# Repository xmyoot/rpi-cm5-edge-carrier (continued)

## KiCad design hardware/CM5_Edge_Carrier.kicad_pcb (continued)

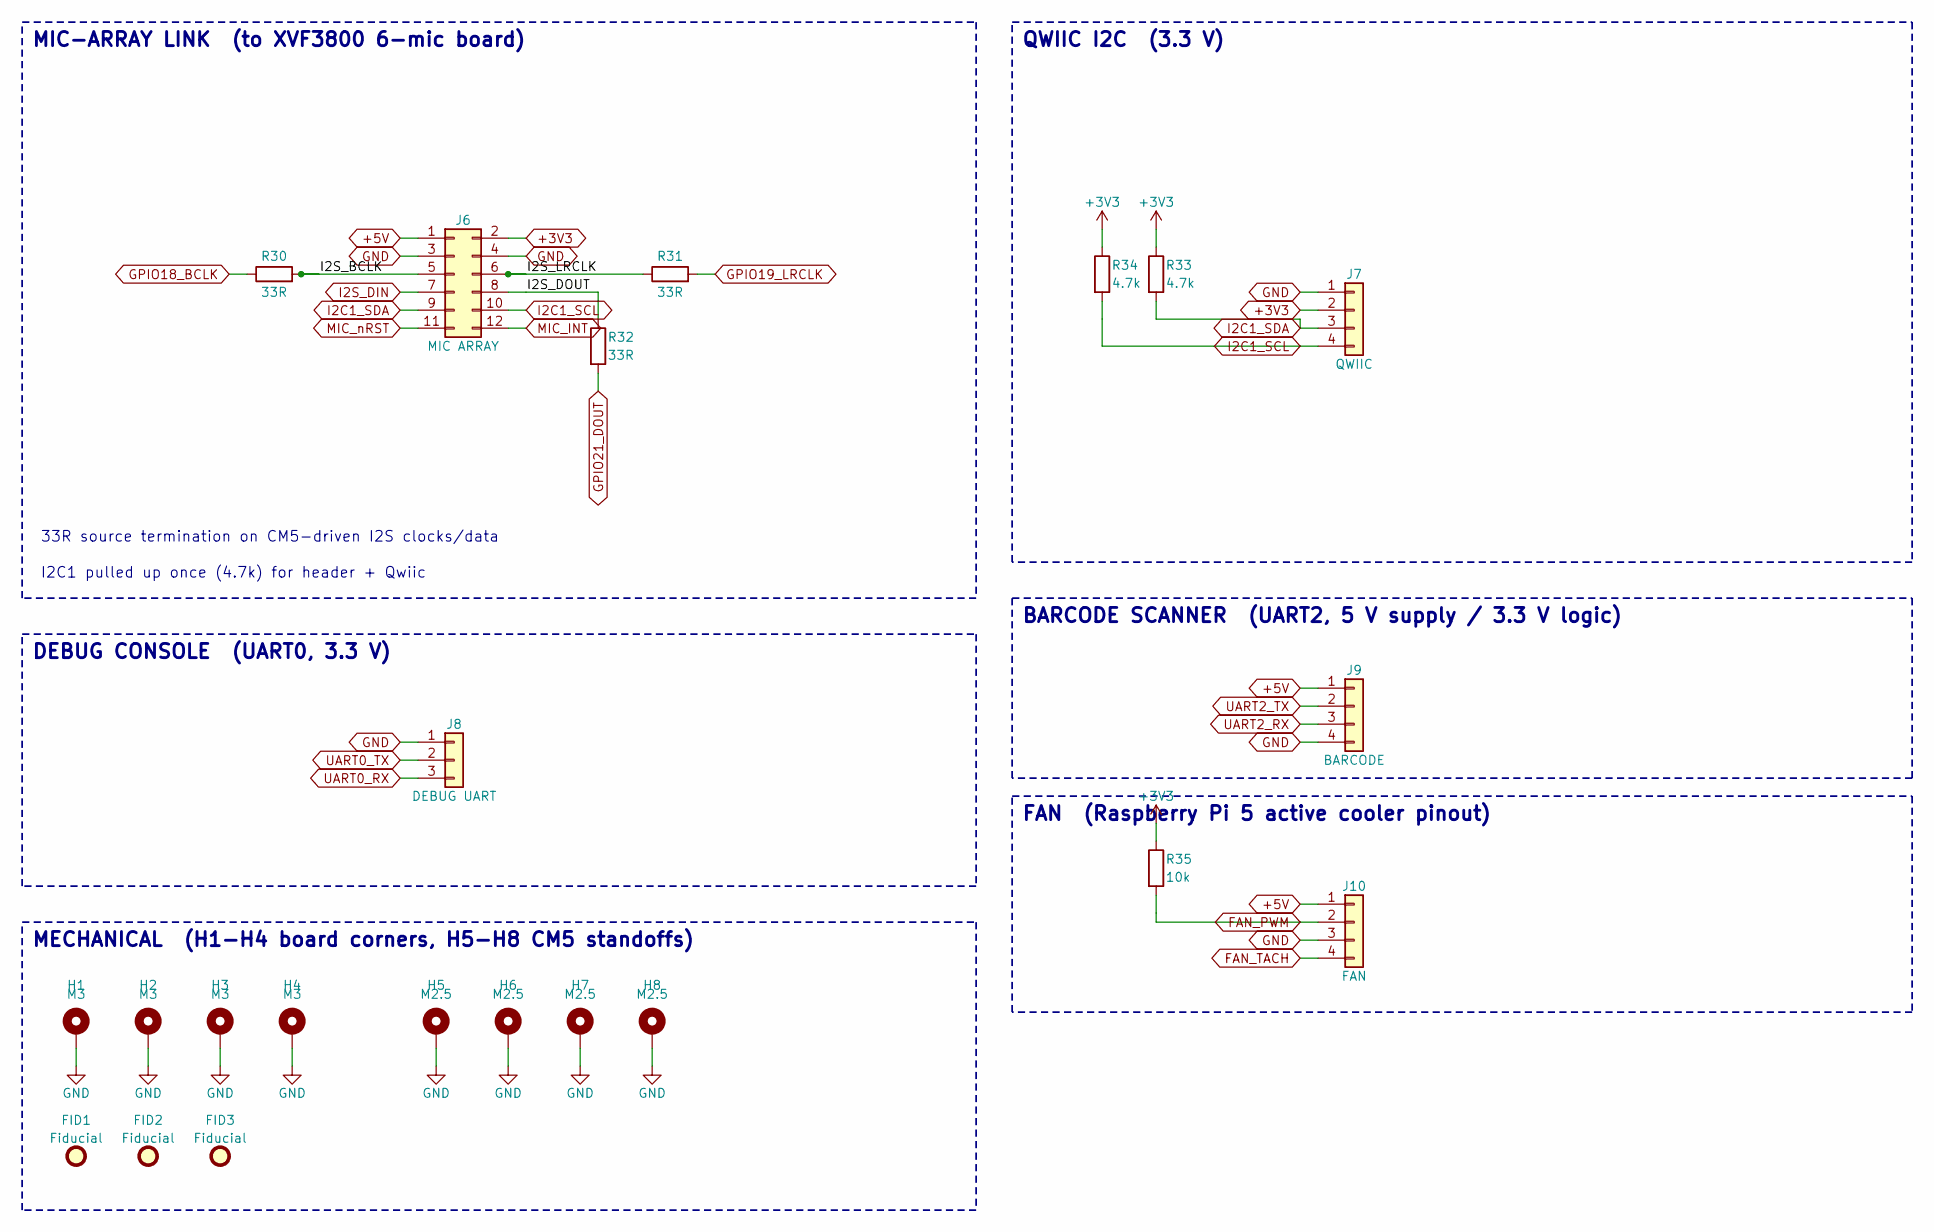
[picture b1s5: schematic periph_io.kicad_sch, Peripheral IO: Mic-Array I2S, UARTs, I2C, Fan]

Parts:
FID1, FID2, FID3: Fiducial; Fiducial_1mm_Mask2mm
H1, H2, H3, H4: M3; MountingHole_3.2mm_M3_Pad_Via
H5, H6, H7, H8: M2.5; MountingHole_2.7mm_M2.5_Pad_Via
J6: MIC ARRAY; IDC-Header_2x06_P2.54mm_Vertical; MPN 2x6 2.54 mm shrouded box header
J7: QWIIC; JST_SH_SM04B-SRSS-TB_1x04-1MP_P1.00mm_Horizontal; MPN JST SM04B-SRSS-TB; LCSC C160404
J8: DEBUG UART; PinHeader_1x03_P2.54mm_Vertical
J9: BARCODE; JST_SH_SM04B-SRSS-TB_1x04-1MP_P1.00mm_Horizontal; MPN JST SM04B-SRSS-TB; LCSC C160404
J10: FAN; JST_SH_SM04B-SRSS-TB_1x04-1MP_P1.00mm_Horizontal; MPN JST SM04B-SRSS-TB; LCSC C160404
R30, R31, R32: 33R; R_0402_1005Metric; Tolerance 1%; LCSC C25105
R33, R34: 4.7k; R_0402_1005Metric; Tolerance 1%; LCSC C25900
R35: 10k; R_0402_1005Metric; Tolerance 1%; LCSC C25744

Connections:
+3V3: J6.2, J7.2, R33.1, R34.1, R35.1; also elsewhere on the board
+5V: J6.1, J9.1, J10.1; also elsewhere on the board
/PeriphIO/I2S_BCLK: J6.5, R30.2
/PeriphIO/I2S_DOUT: J6.8, R32.1
/PeriphIO/I2S_LRCLK: J6.6, R31.1
FAN_PWM: J10.2, R35.2; also elsewhere on the board
FAN_TACH: J10.4; also elsewhere on the board
GND: H1.1, H2.1, H3.1, H4.1, H5.1, H6.1, H7.1, H8.1, J6.3, J6.4, J7.1, J8.1, J9.4, J10.3; also elsewhere on the board
GPIO18_BCLK: R30.1; also elsewhere on the board
GPIO19_LRCLK: R31.2; also elsewhere on the board
GPIO21_DOUT: R32.2; also elsewhere on the board
I2C1_SCL: J6.10, J7.4, R34.2; also elsewhere on the board
I2C1_SDA: J6.9, J7.3, R33.2; also elsewhere on the board
I2S_DIN: J6.7; also elsewhere on the board
MIC_INT: J6.12; also elsewhere on the board
MIC_nRST: J6.11; also elsewhere on the board
UART0_RX: J8.3; also elsewhere on the board
UART0_TX: J8.2; also elsewhere on the board
UART2_RX: J9.3; also elsewhere on the board
UART2_TX: J9.2; also elsewhere on the board

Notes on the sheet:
MIC-ARRAY LINK (to XVF3800 6-mic board)
QWIIC I2C (3.3 V)
DEBUG CONSOLE (UART0, 3.3 V)
BARCODE SCANNER (UART2, 5 V supply / 3.3 V logic)
FAN (Raspberry Pi 5 active cooler pinout)
MECHANICAL (H1-H4 board corners, H5-H8 CM5 standoffs)
33R source termination on CM5-driven I2S clocks/data
I2C1 pulled up once (4.7k) for header + Qwiic

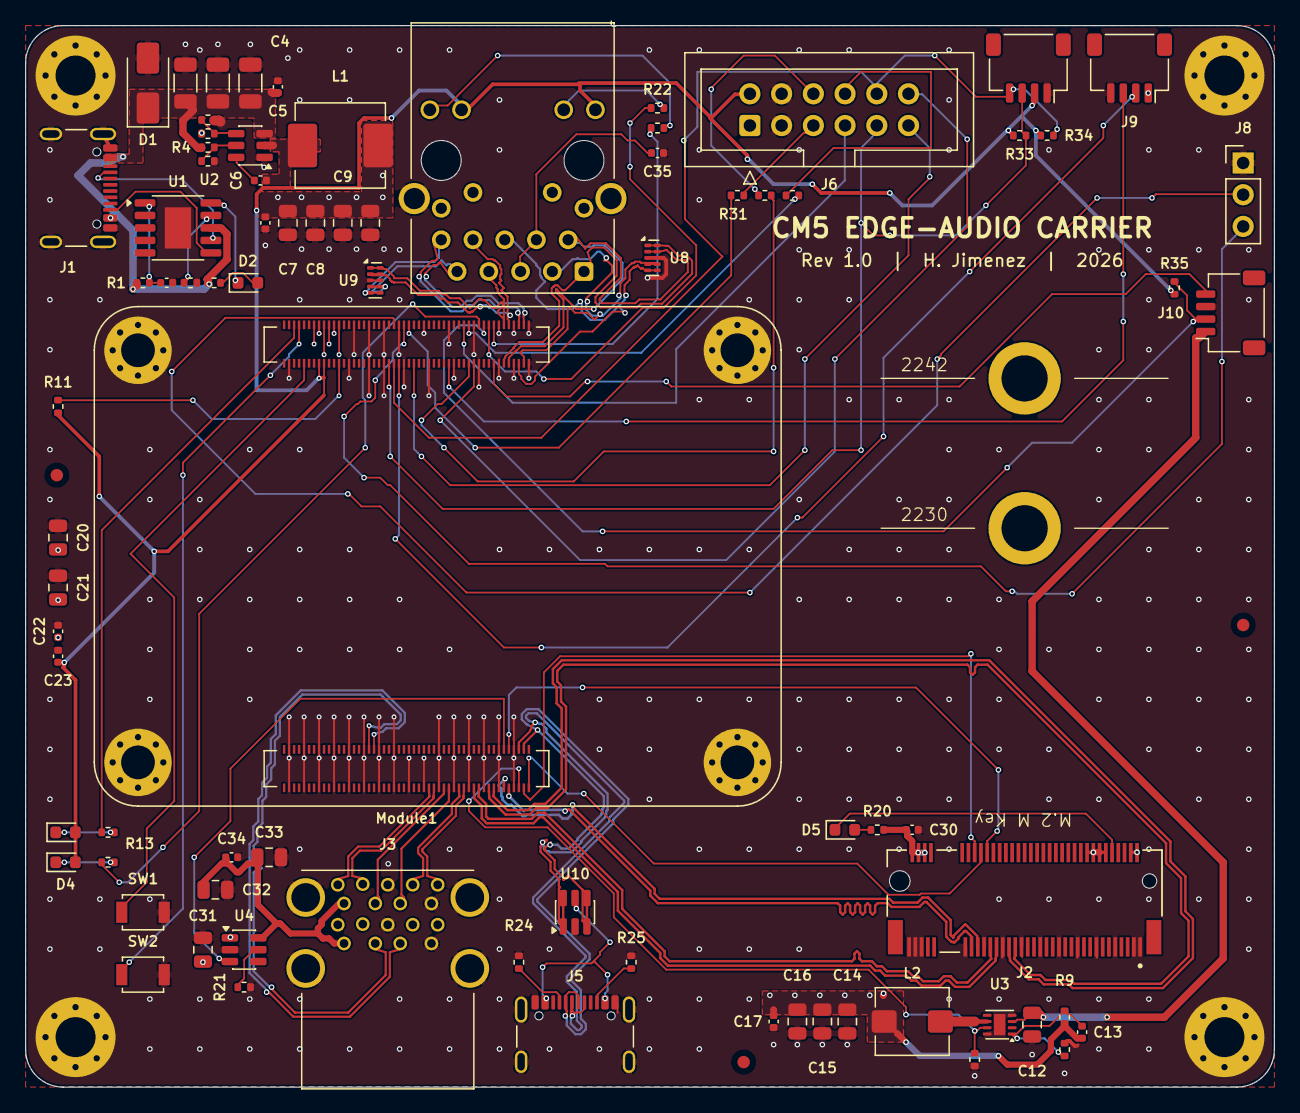
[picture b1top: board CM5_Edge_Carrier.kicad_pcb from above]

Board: 4 copper layers, 100.0 x 85.0 mm, 90 parts (0 on the bottom side), 82 nets.

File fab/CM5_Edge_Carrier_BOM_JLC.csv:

Comment,Designator,Footprint,Quantity,Manufacturer Part,JLCPCB Part #
22uF,"C1,C2,C4",C_1206_3216Metric,3,,C12891
1uF,C3,C_0402_1005Metric,1,,C52923
100nF,"C5,C6,C11,C17,C22,C23,C30,C34,C35",C_0402_1005Metric,9,,C1525
22uF,"C7,C8,C9,C10,C20,C21,C32,C33",C_0805_2012Metric,8,,C45783
10uF,"C12,C14,C15,C16,C31",C_0805_2012Metric,5,,C15850
4.7nF,C13,C_0402_1005Metric,1,,C1538
SMAJ15A,D1,D_SMA,1,Littelfuse SMAJ15A,
PD_OK,D2,LED_0603_1608Metric,1,,C72043
PWR (red),D3,LED_0603_1608Metric,1,,C2286
ACT (green),D4,LED_0603_1608Metric,1,,C72043
SSD (green),D5,LED_0603_1608Metric,1,,C72043
USB-C PD IN,J1,USB_C_Receptacle_GCT_USB4105-xx-A_16P_TopMnt_Horizontal,1,GCT USB4105-GF-A,C3020560
M.2 M-Key (NVMe 2230/2242),J2,M.2_M_Key_2242,1,MTCONN MTSSD03-67MSW337 (H=3.2 mm),
USB 3.0 A x2 (stacked),J3,MTCONN_UBAF30-D2011,1,MTCONN UBAF30-D2011,
RJ45 MagJack 1000BASE-T,J4,TRJG0926HENL,1,Trxcom TRJG0926HENL,
USB-C SERVICE,J5,USB_C_Receptacle_GCT_USB4105-xx-A_16P_TopMnt_Horizontal,1,GCT USB4105-GF-A,C3020560
MIC ARRAY,J6,IDC-Header_2x06_P2.54mm_Vertical,1,2x6 2.54 mm shrouded box header,
QWIIC,J7,JST_SH_SM04B-SRSS-TB_1x04-1MP_P1.00mm_Horizontal,1,JST SM04B-SRSS-TB,C160404
DEBUG UART,J8,PinHeader_1x03_P2.54mm_Vertical,1,,
BARCODE,J9,JST_SH_SM04B-SRSS-TB_1x04-1MP_P1.00mm_Horizontal,1,JST SM04B-SRSS-TB,C160404
FAN,J10,JST_SH_SM04B-SRSS-TB_1x04-1MP_P1.00mm_Horizontal,1,JST SM04B-SRSS-TB,C160404
2.2uH,L1,L_Sunlord_MWSA0603S,1,Sunlord MWSA0603S-2R2MT,
2.2uH,L2,L_Bourns_SRP5030T,1,Bourns SRP5030T-2R2M,
Raspberry Pi CM5,Module1,RPi_CM5_DF40,1,Raspberry Pi CM5 + 2x Hirose DF40C-100DS-0.4V(51),C597931 (x2)
1k,"R1,R12,R13,R20",R_0402_1005Metric,4,,C11702
24k,R2,R_0402_1005Metric,1,,
4.7k,"R3,R33,R34",R_0402_1005Metric,3,,C25900
100k,"R4,R8",R_0402_1005Metric,2,,C25741
15k,"R5,R21",R_0402_1005Metric,2,,C25756
56k,R6,R_0402_1005Metric,1,,C25796
10k,"R7,R9,R35",R_0402_1005Metric,3,,C25744
2.2k,R10,R_0402_1005Metric,1,,C25879
0R,R11,R_0402_1005Metric,1,,C17168
470R,"R22,R23",R_0402_1005Metric,2,,C25117
5.1k,"R24,R25",R_0402_1005Metric,2,,C25905
33R,"R30,R31,R32",R_0402_1005Metric,3,,C25105
POWER,SW1,SW_SPST_B3U-1000P,1,Omron B3U-1000P,C231329
nRPIBOOT,SW2,SW_SPST_B3U-1000P,1,Omron B3U-1000P,C231329
CH224K,U1,SSOP-10-1EP_3.9x4.9mm_P1mm_EP2.1x3.3mm,1,WCH CH224K,C970725
TPS565208,U2,SOT-23-6,1,TI TPS565208DDCR,
AP3441SHE-7B,U3,DFN-8-1EP_2x2mm_P0.5mm_EP0.9x1.7mm,1,Diodes AP3441SHE-7B,
AP22653W6,U4,SOT-23-6,1,Diodes AP22653W6-7,
TPD4EUSB30,"U8,U9",USON-10_2.5x1.0mm_P0.5mm,2,TI TPD4EUSB30DQAR,
USBLC6-2SC6,U10,SOT-23-6,1,ST USBLC6-2SC6,C7519

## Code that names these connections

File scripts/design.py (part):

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    ((332.74, 124.46), 'nRPIBOOT: hold while powering to enter USB boot;'),
    ((332.74, 129.54), 'flash eMMC from a host via USB-C SERVICE (rpiboot).'),
    ((332.74, 137.16), 'PWR_BUT: short press = wake / clean shutdown.'),
    ((332.74, 144.78), 'GPIO bank powered at 3.3 V (GPIO_VREF = +3V3).'),
    ((332.74, 152.4), 'Unused: HDMI0/1, MIPI0/1, SD (eMMC SKU), CAM_GPIO,'),
    ((332.74, 157.48), 'PMIC_ENABLE, EEPROM_nWP, WiFi/BT_nDisable, VBAT.'),
])
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    cm5[p] = 'GND'
for p in (77, 79, 81, 83, 85, 87):
    cm5[p] = '+5V'
cm5.update({84: '+3V3', 86: '+3V3', 78: 'GPIO_VREF',
            3: 'ETH_D3_P', 5: 'ETH_D3_N', 4: 'ETH_D1_P', 6: 'ETH_D1_N',
            9: 'ETH_D2_N', 11: 'ETH_D2_P', 10: 'ETH_D0_N', 12: 'ETH_D0_P',
            15: 'ETH_nLED3', 17: 'ETH_nLED2', 16: 'FAN_TACH', 19: 'FAN_PWM', 21: 'LED_nACT', 95: 'LED_nPWR',
            92: 'PWR_BUT', 93: 'nRPIBOOT',
            56: 'I2C1_SCL', 58: 'I2C1_SDA', 55: 'UART0_TX', 51: 'UART0_RX', 54: 'UART2_TX', 34: 'UART2_RX',
            49: 'GPIO18_BCLK', 26: 'GPIO19_LRCLK', 27: 'I2S_DIN', 25: 'GPIO21_DOUT', 24: 'MIC_INT', 48: 'MIC_nRST',
            103: 'USB2_N', 105: 'USB2_P', 111: 'VBUS_EN',
            102: 'PCIE_nCLKREQ', 104: 'PCIE_nWAKE', 106: 'PCIE_PWR_EN', 109: 'PCIE_nRST',
            110: 'PCIE_CLK_P', 112: 'PCIE_CLK_N', 116: 'PCIE_RX_P', 118: 'PCIE_RX_N', 122: 'PCIE_TX_P', 124: 'PCIE_TX_N',
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for i, (ref, val, net) in enumerate((('C20', '22uF', '+5V'), ('C21', '22uF', '+5V'), ('C22', '100nF', '+5V'),
                                      ('C23', '100nF', '+3V3'))):
    C(M, ref, val, G(10 + 5 * i, 15), net, 'GND')
R(M, 'R11', '0R', G(27, 78), '+3V3', 'GPIO_VREF', rot=90)
FLAG(M, '#FLG06', 'GPIO_VREF', G(22, 74))
R(M, 'R12', '1k', G(140, 16), 'LED_nPWR', 'LED_PWR_K', rot=90)
LED(M, 'D3', 'PWR (red)', G(147, 16), 'LED_PWR_K', '+3V3', 'C2286')
R(M, 'R13', '1k', G(140, 22), 'LED_nACT', 'LED_ACT_K', rot=90)
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            'Connector_IDC:IDC-Header_2x06_P2.54mm_Vertical', G(30, 22), hdr, pin_style={1: 'glabel', 2: 'glabel', 3: 'glabel', 4: 'glabel'},
            fields={'MPN': '2x6 2.54 mm shrouded box header'},
            desc='Mic-array (XVF3800) link: I2S + I2C control + reset/IRQ'))
R(I, 'R30', '33R', G(20, 22), 'GPIO18_BCLK', 'I2S_BCLK', rot=90)
R(I, 'R31', '33R', G(42, 22), 'I2S_LRCLK', 'GPIO19_LRCLK', rot=90)
R(I, 'R32', '33R', G(38, 26), 'I2S_DOUT', 'GPIO21_DOUT')
R(I, 'R33', '4.7k', G(69, 22), '+3V3', 'I2C1_SDA')
R(I, 'R34', '4.7k', G(66, 22), '+3V3', 'I2C1_SCL')
add(I, Part('J7', 'Connector_Generic:Conn_01x04', 'QWIIC', JSTSH4, G(80, 24),
            {1: 'GND', 2: '+3V3', 3: 'I2C1_SDA', 4: 'I2C1_SCL'}, pin_style={1: 'glabel', 2: 'glabel'},
            fields={'MPN': 'JST SM04B-SRSS-TB', 'LCSC': 'C160404'}))
add(I, Part('J8', 'Connector_Generic:Conn_01x03', 'DEBUG UART', 'Connector_PinHeader_2.54mm:PinHeader_1x03_P2.54mm_Vertical',
            G(30, 49), {1: 'GND', 2: 'UART0_TX', 3: 'UART0_RX'}, pin_style={1: 'glabel'}))
add(I, Part('J9', 'Connector_Generic:Conn_01x04', 'BARCODE', JSTSH4, G(80, 46),
            {1: '+5V', 2: 'UART2_TX', 3: 'UART2_RX', 4: 'GND'}, pin_style={1: 'glabel', 4: 'glabel'},
            fields={'MPN': 'JST SM04B-SRSS-TB', 'LCSC': 'C160404'}))
add(I, Part('J10', 'Connector_Generic:Conn_01x04', 'FAN', JSTSH4, G(80, 58),
            {1: '+5V', 2: 'FAN_PWM', 3: 'GND', 4: 'FAN_TACH'}, pin_style={1: 'glabel', 3: 'glabel'},
            fields={'MPN': 'JST SM04B-SRSS-TB', 'LCSC': 'C160404'}))
R(I, 'R35', '10k', G(69, 55), '+3V3', 'FAN_PWM')
for i in range(4):
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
